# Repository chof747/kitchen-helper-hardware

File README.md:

# kitchen-helper-hardware
Hardware specs, schematics and pcb design for the kitchen helper device

The KitchenHelper consists of the following features:

- ESP32-S3 MCU 
- TFT Display
- 2 push buttons and a rotary encoder
- 2 cinch slots for NTC temperature sensors
- Buzzer to play sounds
- An addressable led row to show status information and progressy
- Battery and power management 
- Programming Header

## Verification

1. [Done] Programming Header 
2. [Done] Display
3. [Done] Buzzer
4. [Done] Push Buttons

5. [Open] Power and Battery Management
   - protection ICs
   - Voltage regulation
   - charging with charger board

6. [Open] Rotary Encoder schematic 
   - pull-up circuit

7. [Open] Addressable Status Leds 
   - level shifting, 
   - voltage from Battery

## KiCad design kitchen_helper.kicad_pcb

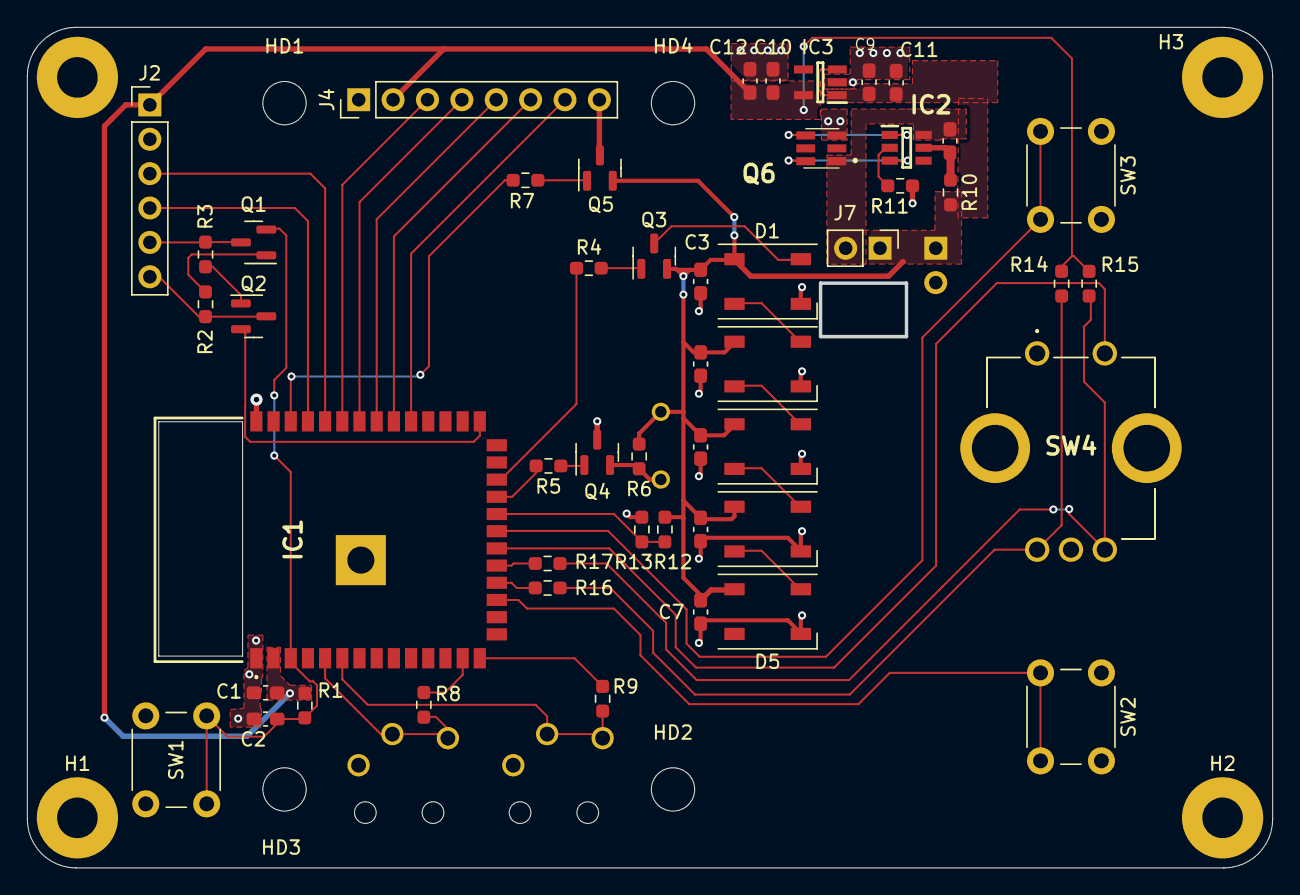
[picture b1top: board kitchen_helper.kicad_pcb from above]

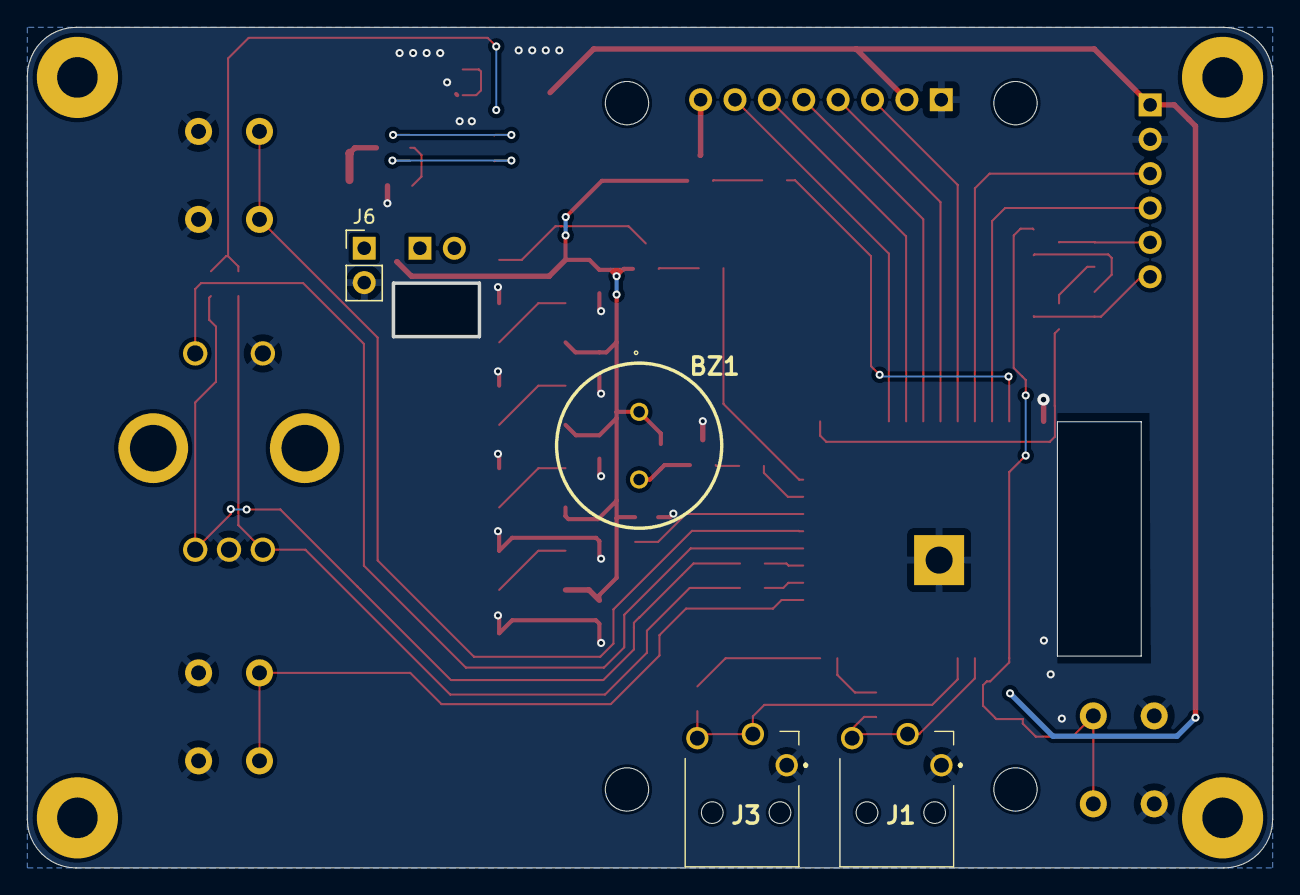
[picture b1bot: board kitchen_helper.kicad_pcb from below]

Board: 2 copper layers, 91.8 x 61.9 mm, 62 parts (4 on the bottom side), 46 nets.

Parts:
BZ1: Buzzer; PS1240P02BT
C1: 10uF; C_0603_1608Metric_Pad1.08x0.95mm_HandSolder
C2, C9, C10, C11, C12: 1uF; C_0603_1608Metric_Pad1.08x0.95mm_HandSolder
C3, C4, C5, C6, C7: 100nF; C_0603_1608Metric_Pad1.08x0.95mm_HandSolder
C8: 0.1uF; C_0603_1608Metric_Pad1.08x0.95mm_HandSolder
D1, D2, D3, D4, D5: WS2812B; LED_WS2812B_PLCC4_5.0x5.0mm_P3.2mm
H1, H2, H3, H4: MountingHole; MountingHole_3mm_Pad
HD1, HD2, HD3, HD4: MountingHole; MountingHole_3.2mm_M3
IC1: ESP32-S3-WROOM-1-N8R8; ESP32S3WROOM1N8R8
IC2: FS312F-G; SOT95P280X145-6N
IC3: VReg 3v3; SOT95P270X145-5N
J1: Temp 1; MJ2509N
J2: PROG_HDR; PinHeader_1x06_P2.54mm_Vertical
J3: Temp 2; MJ2509N
J4: DISP_HDR; PinHeader_1x08_P2.54mm_Vertical
J6: Charger; PinHeader_1x02_P2.54mm_Vertical
J7: Battery; PinHeader_1x02_P2.54mm_Vertical
Q1, Q2, Q3, Q4, Q5: SS8050-G; SOT-23
Q6: FS8205
R1, R12, R13, R14, R15: 22k; R_0603_1608Metric_Pad0.98x0.95mm_HandSolder
R2, R3: 10k; R_0603_1608Metric_Pad0.98x0.95mm_HandSolder
R4, R5, R6, R7, R16, R17: 1k; R_0603_1608Metric_Pad0.98x0.95mm_HandSolder
R8, R9: 100k; R_0603_1608Metric_Pad0.98x0.95mm_HandSolder
R10: 100; R_0603_1608Metric_Pad0.98x0.95mm_HandSolder
R11: 2k; R_0603_1608Metric_Pad0.98x0.95mm_HandSolder
SW1: SW_Reset; SW_PUSH_6mm
SW2: BTN_LEFT; SW_PUSH_6mm
SW3: BTN_RIGHT; SW_PUSH_6mm
SW4: RotaryEncoder_Switch; PEC12R3120FS0012

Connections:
GPIO0: IC1.27 (IO0), Q2.2 (C)
+3V3: C1.1, C10.1, C12.1, IC1.2 (3V3), IC3.5 (VOUT), J2.1, J4.2, R1.1, R14.2, R15.2
/BATT+: BZ1.1 (-), C3.1, C4.1, C5.1, C6.1, C7.1, C9.1, C11.1, D1.1 (VDD), D2.1 (VDD), D3.1 (VDD), D4.1 (VDD), D5.1 (VDD), IC3.1 (VIN), IC3.3 (CE), J6.1, J7.1, Q3.2 (C), Q5.2 (C), R6.2, R10.2, R12.1
/BTNLEFT_IO9: IC1.17 (IO9), SW2.2
/BTNRGHT_IO13: IC1.21 (IO13), SW3.2
/I40_DISPLAY_RESET: IC1.33 (IO40), J4.5
/IO02_DISPLAY_BKLT: IC1.38 (IO2), R7.2
/IO19_ADC_DRV0: IC1.13 (IO19), R8.1
/IO19_ADC_DRV1: IC1.14 (IO20), R9.1
/IO21_PWM_BUZZ: IC1.23 (IO21), R5.1
/IO38_DISPLAY_CS: IC1.31 (IO38), J4.7
/IO39_DISPLAY_RS: IC1.32 (IO39), J4.6
/IO41_DISPLAY_SDA: IC1.34 (IO41), J4.4
/IO42_DISPLAY_SCK: IC1.35 (IO42), J4.3
/IO47_LEDS_DAT: IC1.24 (IO47), R4.2
/Power Management/BATT-: C8.2, IC2.6 (GND), J7.2, Q6.1 (S1)
/Power Management/Bat-In: C8.1, IC2.5 (VCC), R10.1
/Power Management/CurrSense: IC2.2 (CS), R11.1
/Power Management/OvrChg: IC2.3 (OC), Q6.4 (G2)
/Power Management/OvrDisChg: IC2.1 (OD), Q6.6 (G1)
/REN_BTN_IO12: IC1.20 (IO12), SW4.2 (NO)
/REN_CLK_IO10: IC1.18 (IO10), R16.1
/REN_DAT_IO11: IC1.19 (IO11), R17.1
/TEMP1_AIO5: IC1.5 (IO5), J1.2, J1.3, R8.2
/TEMP2_AIO6: IC1.6 (IO6), J3.2, J3.3, R9.2
/VBat-Check: IC1.22 (IO14), R12.2, R13.1
DTR: J2.6, Q2.3 (E), R2.1
ESP32_RX: IC1.36 (RXD0), J2.3
ESP32_TX: IC1.37 (TXD0), J2.4
GND: C1.2, C2.2, C3.2, C4.2, C5.2, C6.2, C7.2, C9.2, C10.2, C11.2, C12.2, D1.3 (VSS), D2.3 (VSS), D3.3 (VSS), D4.3 (VSS), D5.3 (VSS), IC1.1 (GND_1), IC3.2 (VSS), J1.1, J2.2, J3.1, J4.1, J6.2, Q4.3 (E), Q6.3 (S2), R11.2, R13.2, SW1.1, SW2.1, SW3.1, SW4.1 (COM), SW4.C1 (COMMON)
unnamed: BZ1.2 (+), Q4.2 (C), R6.1
unnamed: D1.2 (DOUT), D2.4 (DIN)
unnamed: D1.4 (DIN), Q3.3 (E)
unnamed: D2.2 (DOUT), D3.4 (DIN)
unnamed: D3.2 (DOUT), D4.4 (DIN)
unnamed: D4.2 (DOUT), D5.4 (DIN)
unnamed: J4.8, Q5.3 (E)
unnamed: Q1.1 (B), R2.2
unnamed: Q2.1 (B), R3.2
unnamed: Q3.1 (B), R4.1
unnamed: Q4.1 (B), R5.2
unnamed: Q5.1 (B), R7.1
unnamed: R14.1, R16.2, SW4.A1 (CHANNEL_A)
unnamed: R15.1, R17.2, SW4.B1 (CHANNEL_B)
RTS: J2.5, Q1.3 (E), R3.1
~RESET: C2.1, IC1.3 (EN), Q1.2 (C), R1.2, SW1.2

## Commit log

2022-10-31 Initial version of kitchen helper hardware
2022-11-29 Modifications for ADC ports
    - Changed voltage divider resistor to 100k
    - Changed the voltage supply for the ADC pins from 3v3 to a GPIO Pin to turn them on only as needeed.
    - Deleted some old files
2023-01-11 Put components and verification into README.md
2023-01-13 Corrected issues found during schematic verification
    - splitted driving lines for both temperature sensors to prevent nfluencing through parallel resistance
    - swaped the two directions of the rotary encoder
    - Powering the TFT backlight from BATT+ as the voltage drop at the resistor is too much for 3v3
    - Added resistor network to directly pull rotary encorder to 3v3
2023-01-13 Late save of schema file^:
2023-04-27 Migrated project to KiCad7
